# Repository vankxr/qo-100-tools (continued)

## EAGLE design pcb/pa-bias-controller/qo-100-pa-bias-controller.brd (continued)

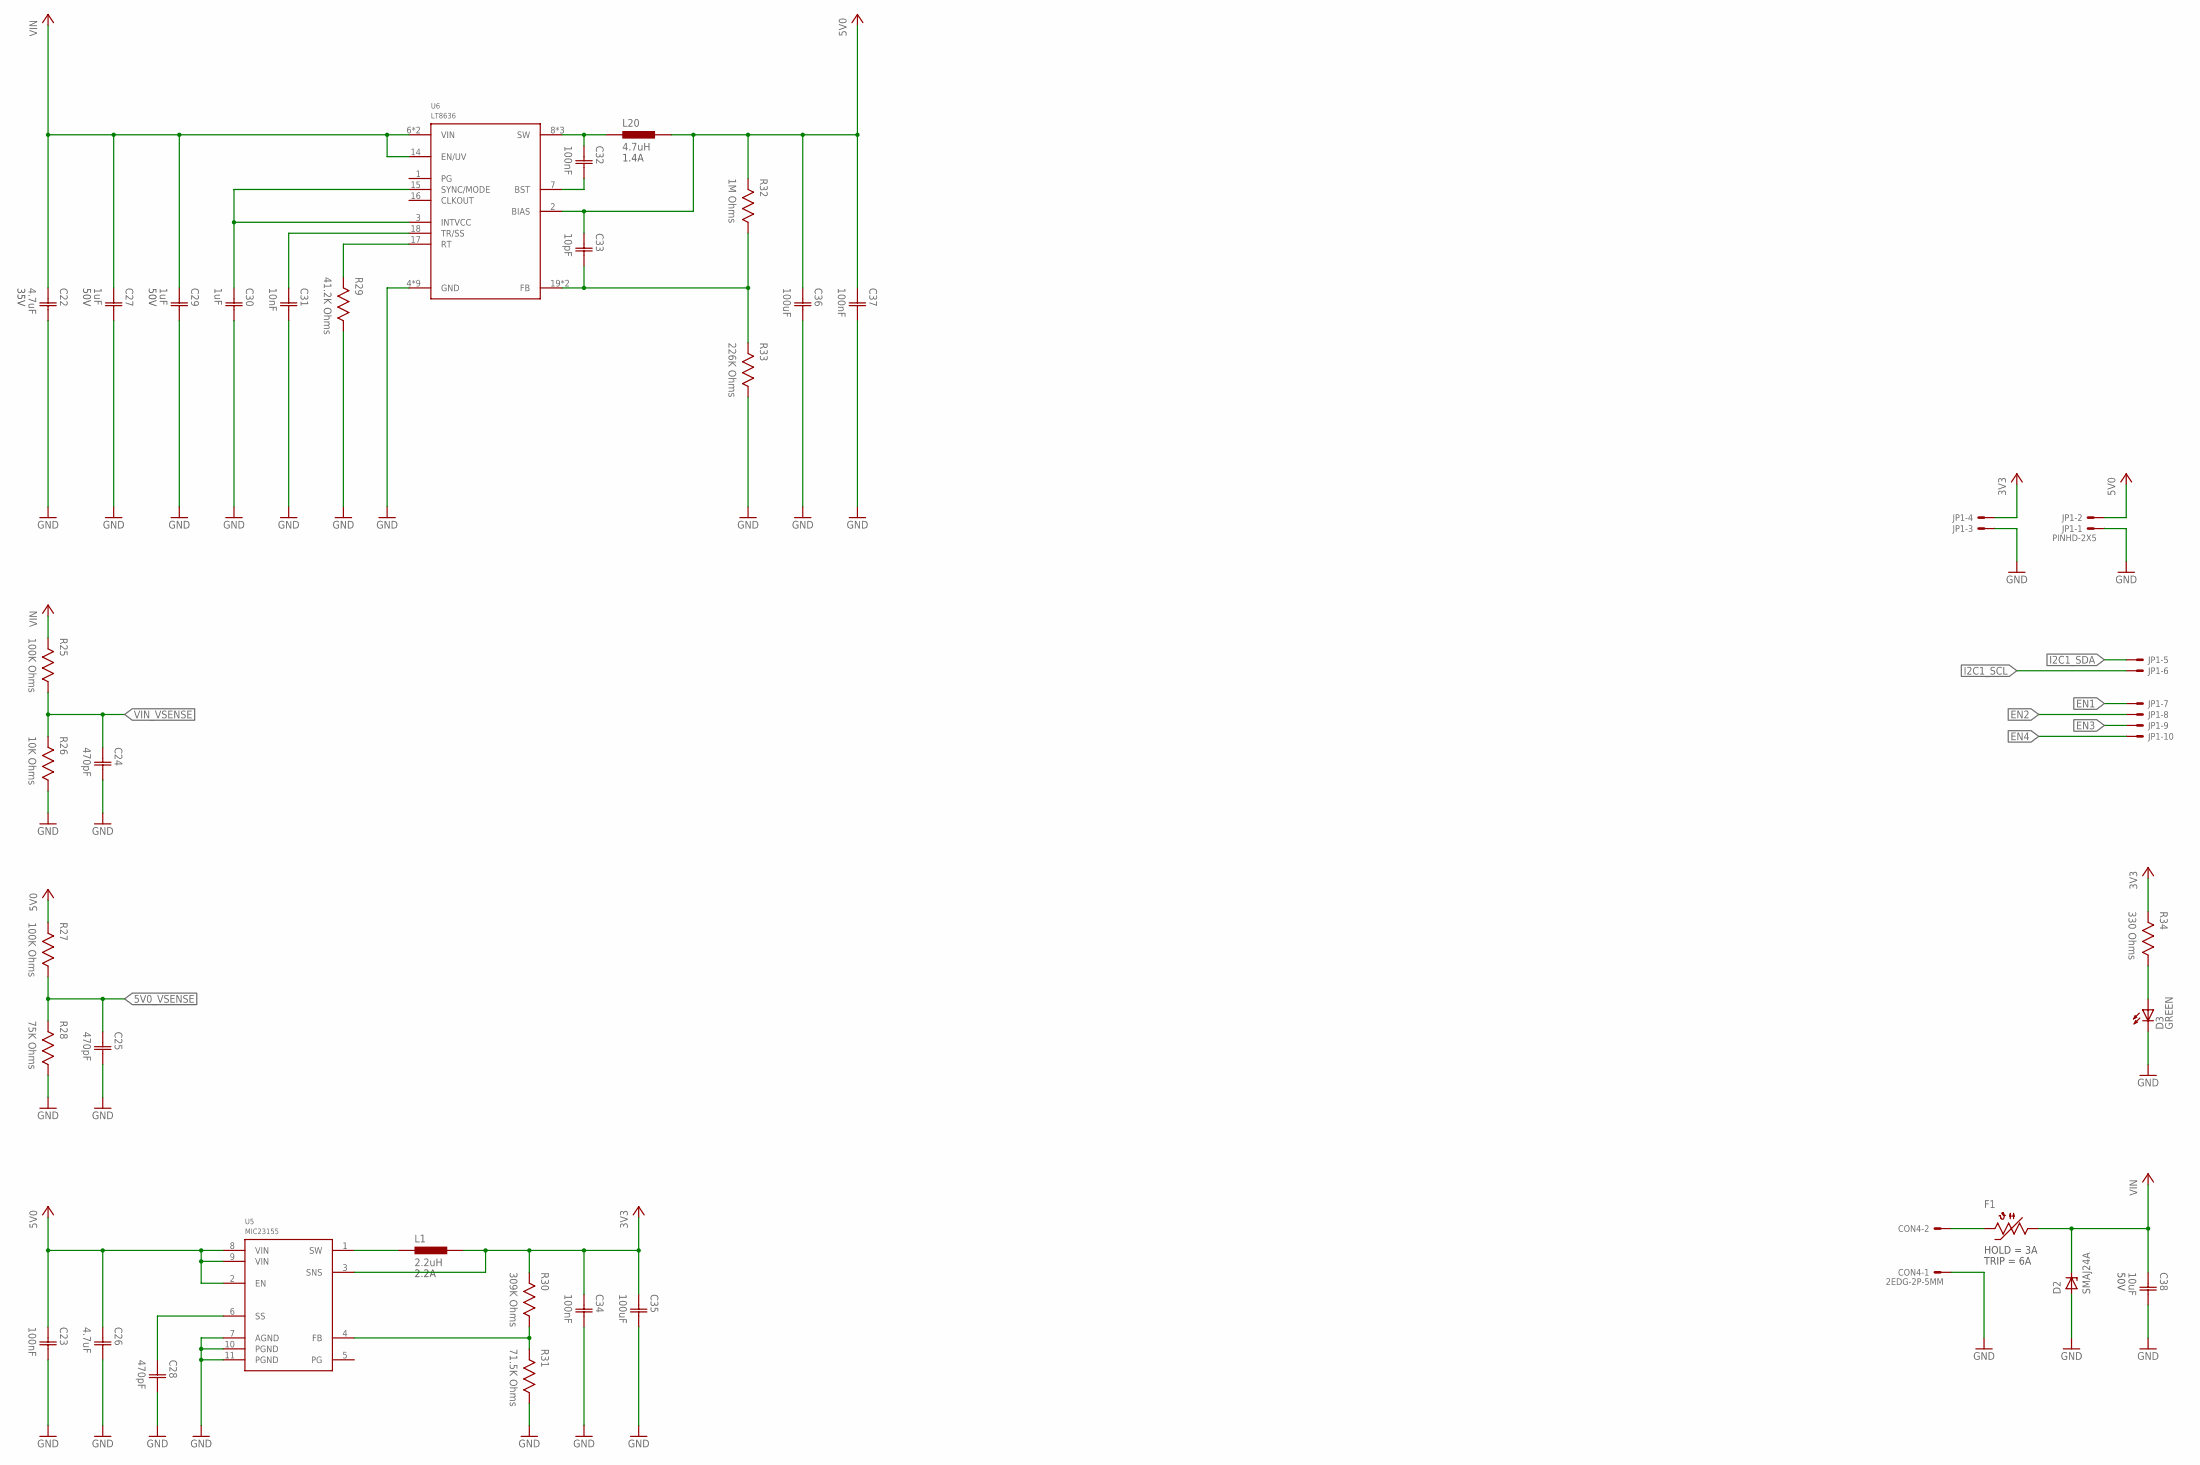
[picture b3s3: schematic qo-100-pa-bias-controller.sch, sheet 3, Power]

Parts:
C22: 4.7uF; CAP0603; VOLTAGE 35V
C23, C32, C34, C37: 100nF; CAP0603
C24, C25, C28: 470pF; CAP0603
C26: 4.7uF; CAP0603
C27, C29: 1uF; CAP0603; VOLTAGE 50V
C30: 1uF; CAP0603
C31: 10nF; CAP0603
C33: 10pF; CAP0603
C35, C36: 100uF; CAP1206
C38: 10uF; CAP1206; VOLTAGE 50V
CON4: 2EDG-2P-5MM
D2: SMAJ24A; DO214AC
D3: LED0603; 0603
F1: 2.6A Hold; 1206
JP1: PINHD-2X5; 2X05
L1: 2.2uH; IND2520
L20: 4.7uH; IND2520
R25, R27: 100K Ohms; RES0603
R26: 10K Ohms; RES0603
R28: 75K Ohms; RES0603
R29: 41.2K Ohms; RES0603
R30: 309K Ohms; RES0603
R31: 71.5K Ohms; RES0603
R32: 1M Ohms; RES0603
R33: 226K Ohms; RES0603
R34: 330 Ohms; RES0603
U5: MIC23155; DFN10
U6: LT8636; QFN20_ASYM_CORNER

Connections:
3V3: C34.1 (C1), C35.1 (C1), JP1.4, L1.2, R30.2, R34.2, U5.3 (SNS); also elsewhere on the board
3V3_FB: R30.1, R31.2, U5.4 (FB)
3V3_SOFTSTART: C28.1 (C1), U5.6 (SS)
3V3_SW: L1.1, U5.1 (SW)
5V0: C23.1 (C1), C26.1 (C1), C33.1 (C1), C36.1 (C1), C37.1 (C1), JP1.2, L20.2, R27.2, R32.2, U5.2 (EN), U5.8 (VIN), U5.9 (VIN), U6.2 (BIAS); also elsewhere on the board
5V0_BST: C32.2 (C2), U6.7 (BST)
5V0_FB: C33.2 (C2), R32.1, R33.2, U6.19 (FB), U6.20 (FB)
5V0_INTVCC: C30.1 (C1), U6.3 (INTVCC), U6.15 (SYNC/MODE)
5V0_RT: R29.2, U6.17 (RT)
5V0_SS: C31.1 (C1), U6.18 (TR/SS)
5V0_SW: C32.1 (C1), L20.1, U6.8 (SW), U6.9 (SW), U6.10 (SW)
5V0_VSENSE: C25.1 (C1), R27.1, R28.2; also elsewhere on the board
EN1: JP1.7; also elsewhere on the board
EN2: JP1.8; also elsewhere on the board
EN3: JP1.9; also elsewhere on the board
EN4: JP1.10; also elsewhere on the board
GND: C22.2 (C2), C23.2 (C2), C24.2 (C2), C25.2 (C2), C26.2 (C2), C27.2 (C2), C28.2 (C2), C29.2 (C2), C30.2 (C2), C31.2 (C2), C34.2 (C2), C35.2 (C2), C36.2 (C2), C37.2 (C2), C38.2 (C2), CON4.P$1, D2.A, D3.C, JP1.1, JP1.3, R26.1, R28.1, R29.1, R31.1, R33.1, U5.7 (AGND), U5.10 (PGND), U5.11 (PGND), U6.4 (GND), U6.5 (GND), U6.12 (GND), U6.13 (GND), U6.21 (GND), U6.M1 (GND), U6.M2 (GND), U6.M3 (GND), U6.M4 (GND); also elsewhere on the board
I2C1_SCL: JP1.6; also elsewhere on the board
I2C1_SDA: JP1.5; also elsewhere on the board
unnamed: CON4.P$2, F1.2
unnamed: D3.A, R34.1
VIN: C22.1 (C1), C27.1 (C1), C29.1 (C1), C38.1 (C1), D2.C, F1.1, R25.2, U6.6 (VIN), U6.11 (VIN), U6.14 (EN/UV)
VIN_VSENSE: C24.1 (C1), R25.1, R26.2; also elsewhere on the board

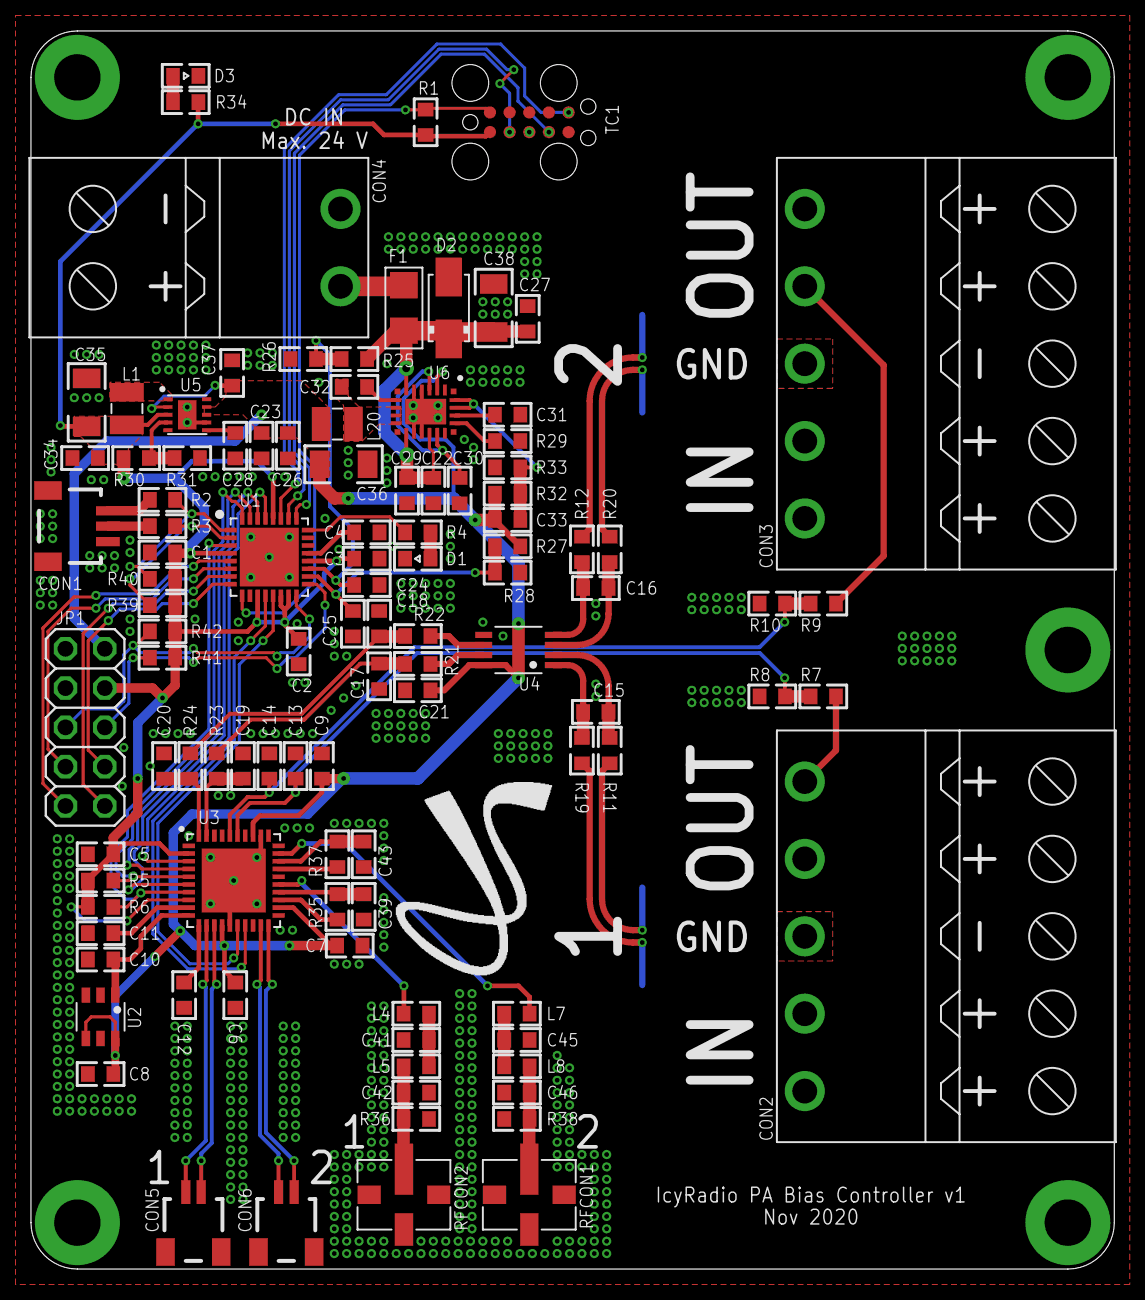
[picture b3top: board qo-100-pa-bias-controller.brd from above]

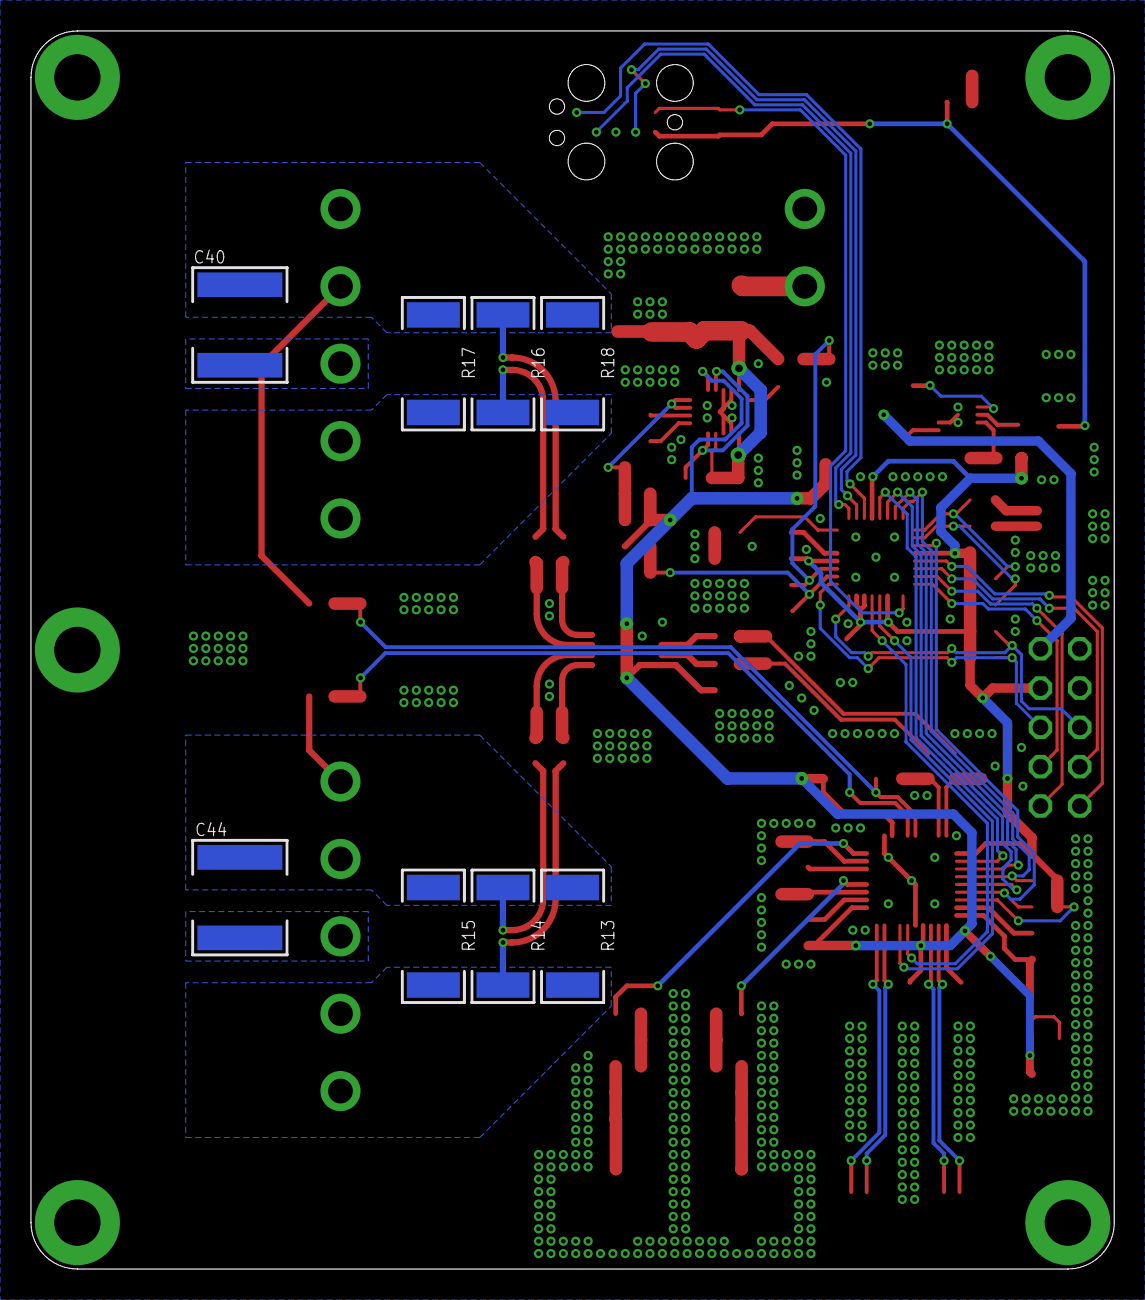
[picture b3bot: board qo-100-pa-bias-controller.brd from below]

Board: 2 copper layers, 70.0 x 80.0 mm, 115 parts (8 on the bottom side), 74 nets.

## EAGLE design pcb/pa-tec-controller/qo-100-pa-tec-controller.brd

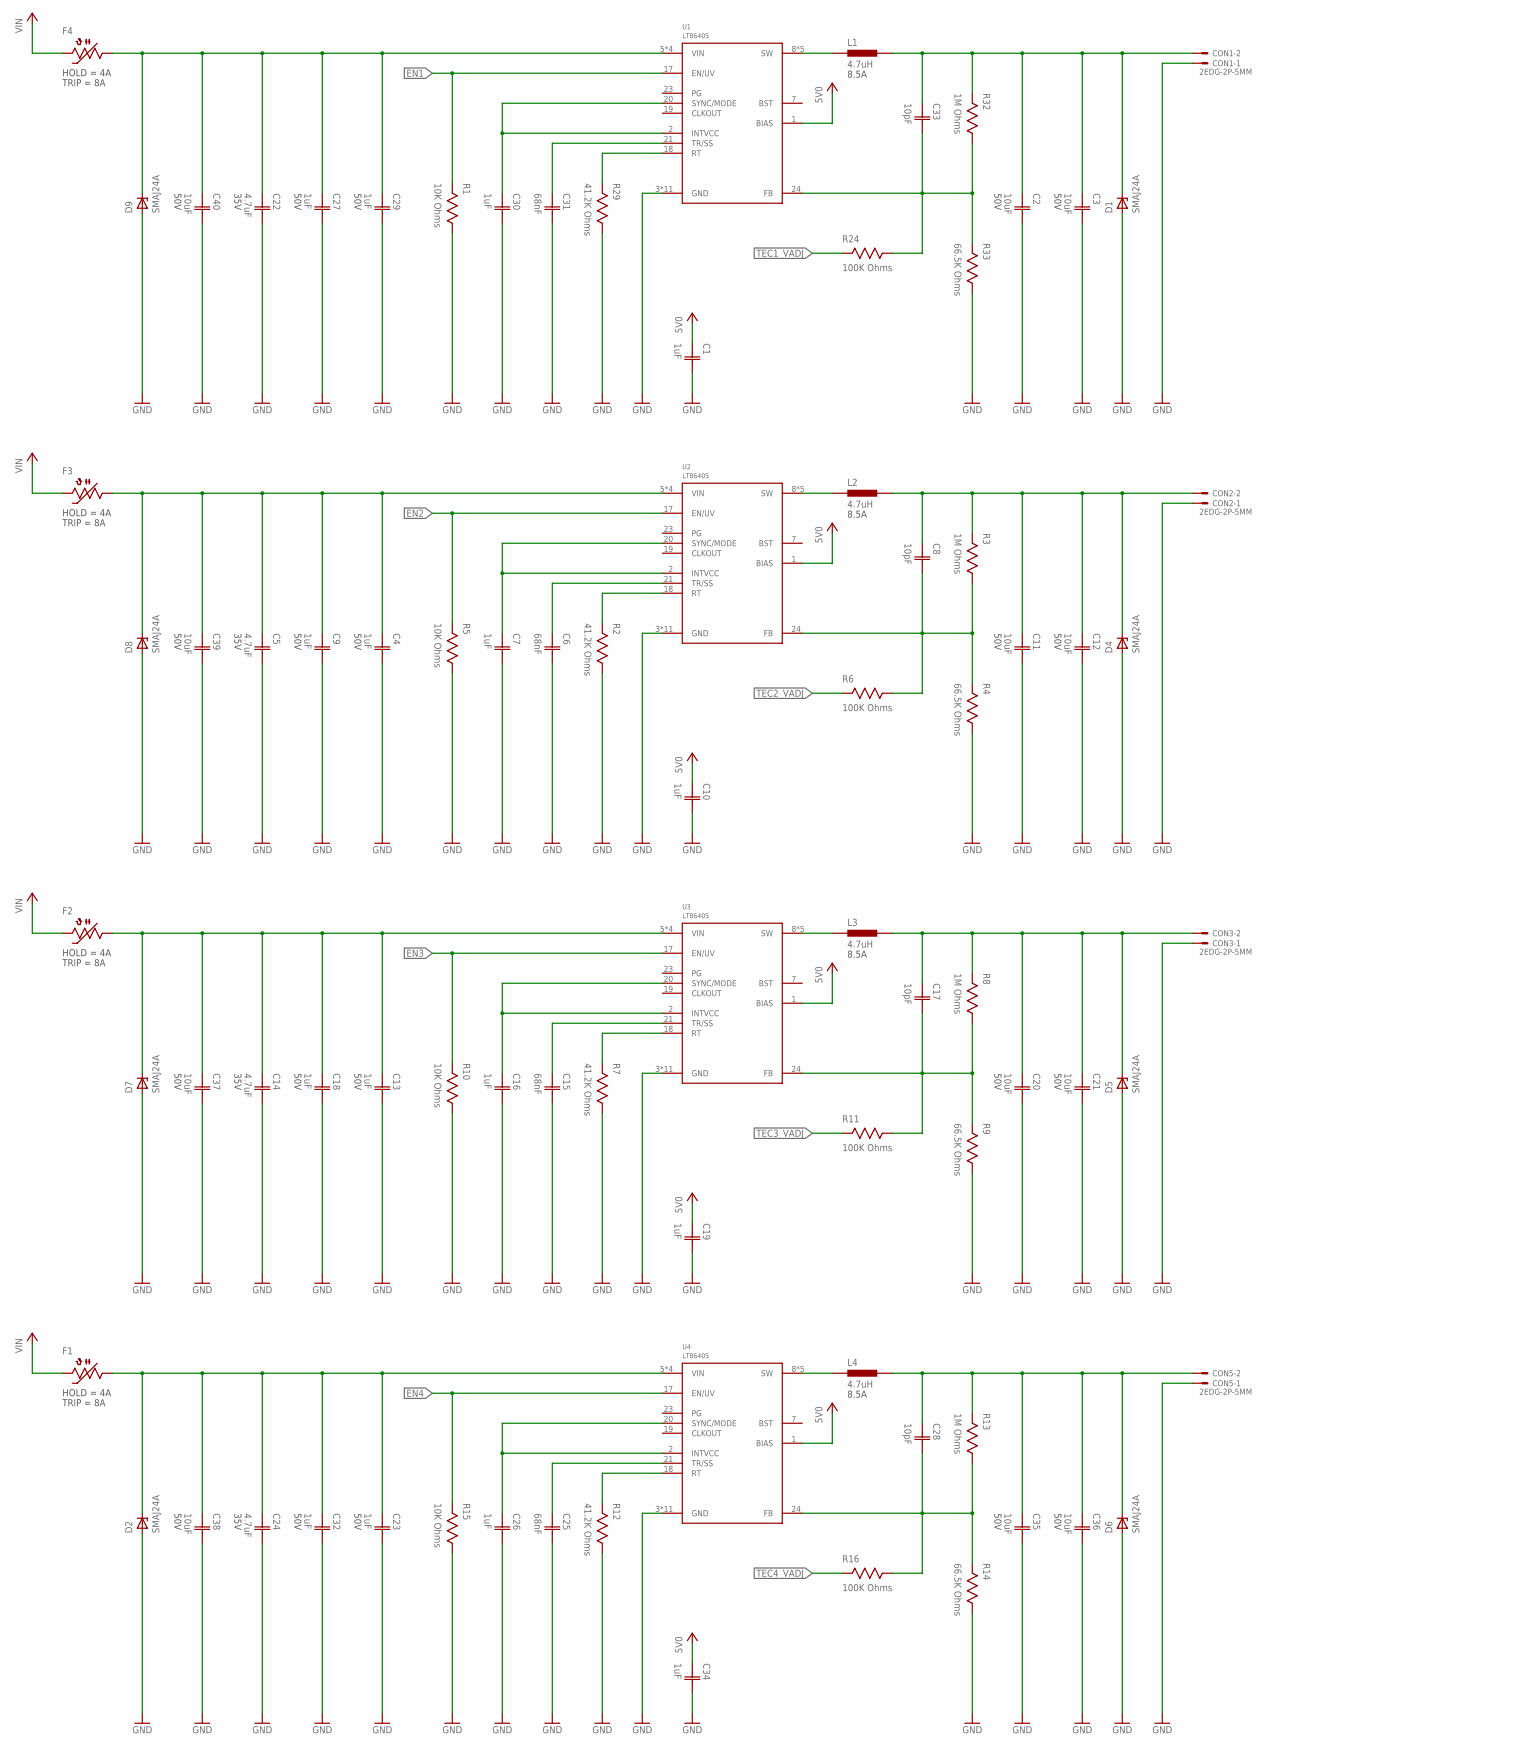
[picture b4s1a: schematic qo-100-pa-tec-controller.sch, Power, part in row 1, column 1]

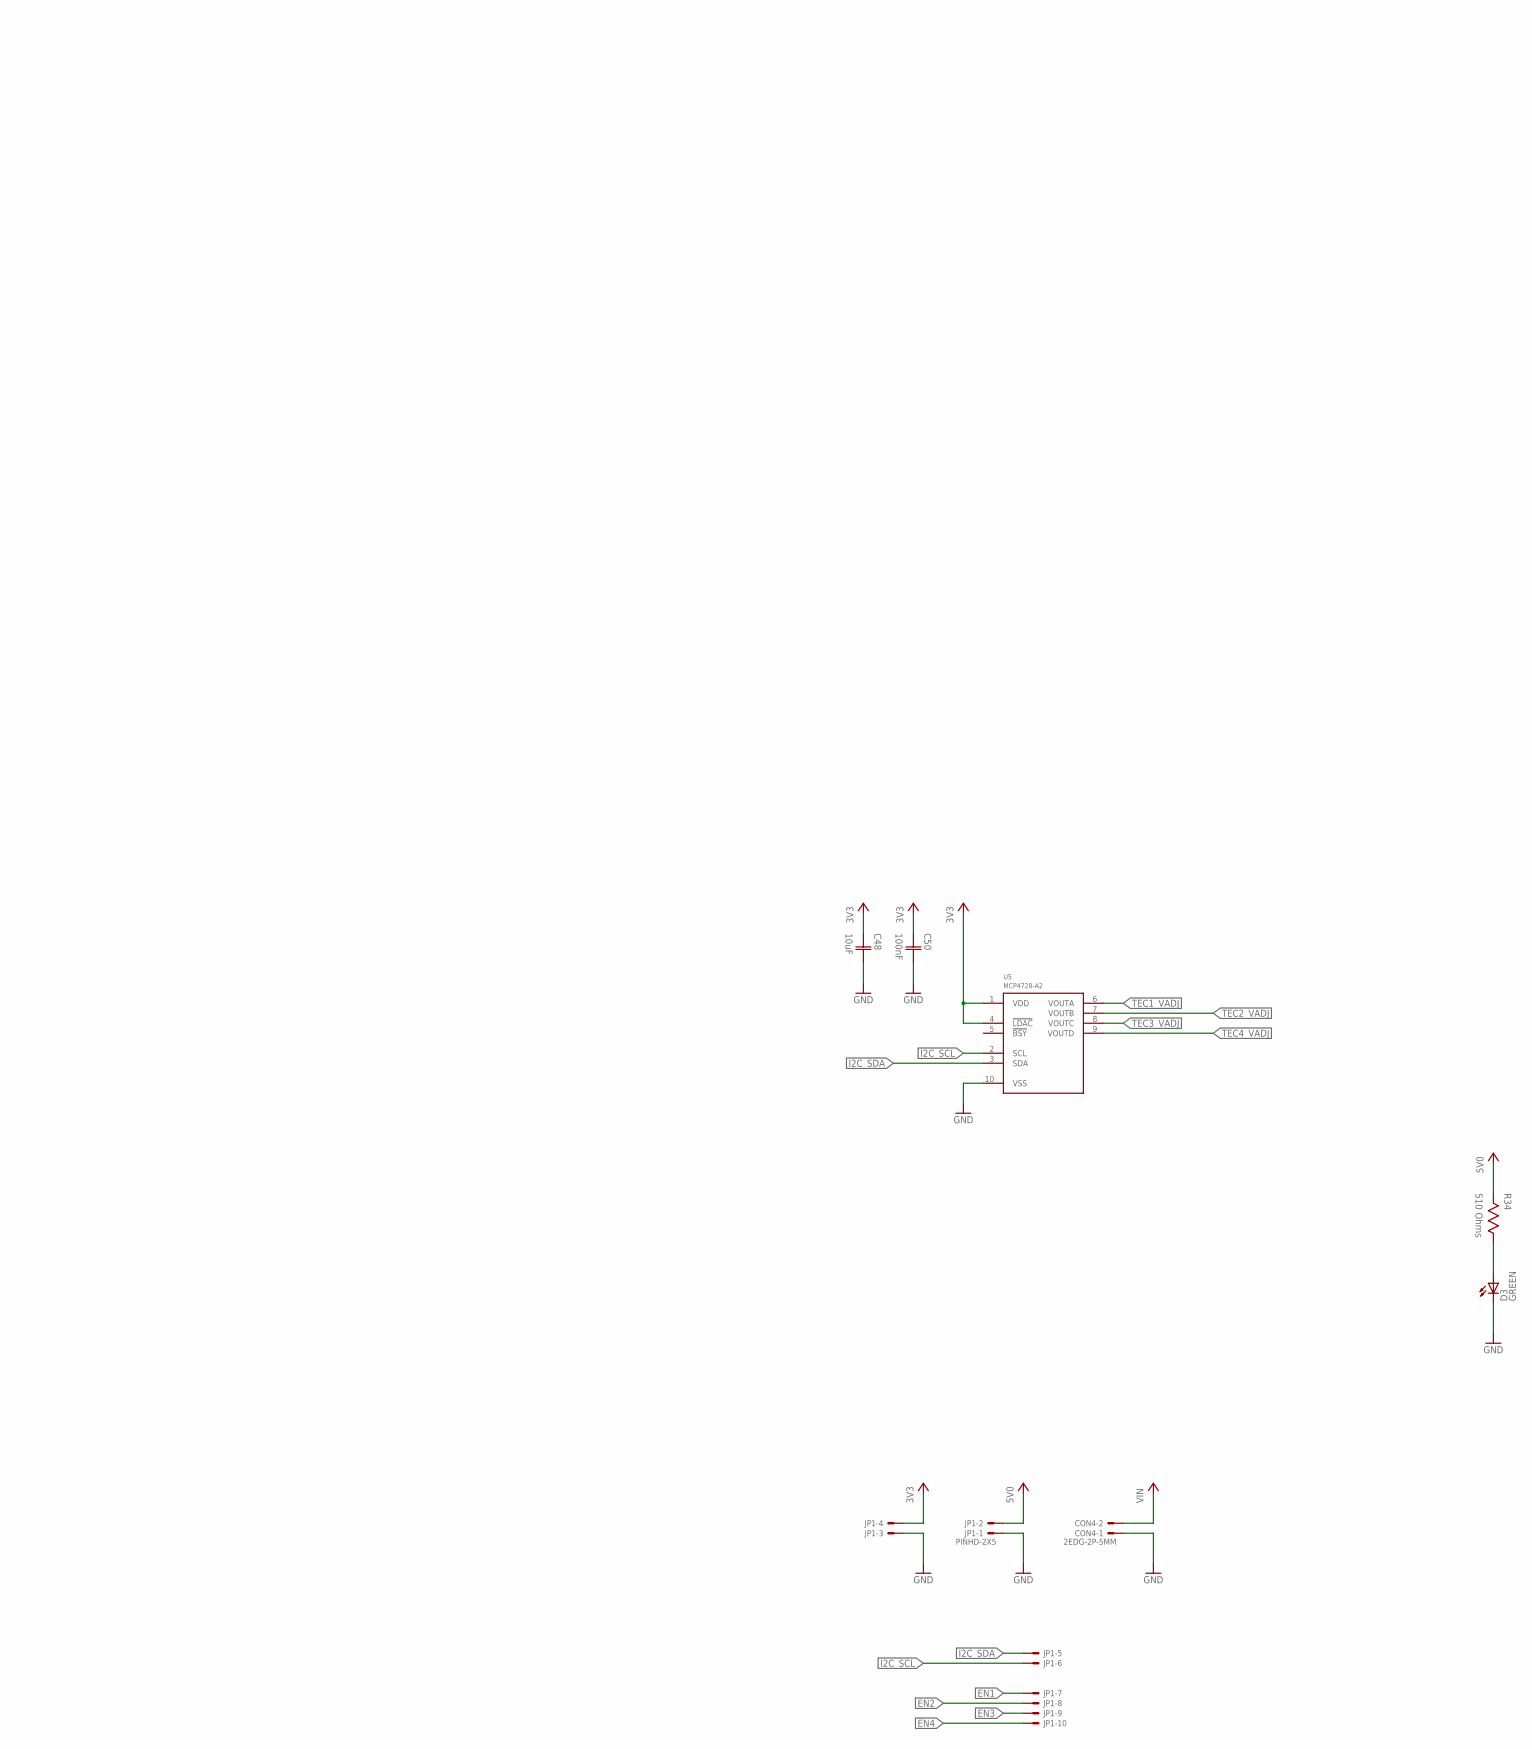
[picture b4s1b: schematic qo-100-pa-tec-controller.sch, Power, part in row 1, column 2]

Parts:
C1, C7, C10, C16, C19, C26, C30, C34: 1uF; CAP0603
C2, C3, C11, C12, C20, C21, C35, C36, C37, C38, C39, C40: 10uF; CAP1206; VOLTAGE 50V
C4, C9, C13, C18, C23, C27, C29, C32: 1uF; CAP0603; VOLTAGE 50V
C5, C14, C22, C24: 4.7uF; CAP0603; VOLTAGE 35V
C6, C15, C25, C31: 68nF; CAP0603
C8, C17, C28, C33: 10pF; CAP0603
C48: 10uF; CAP0603
C50: 100nF; CAP0603
CON1, CON2, CON3, CON4, CON5: 2EDG-2P-5MM
D1, D2, D4, D5, D6, D7, D8, D9: SMAJ24A; DO214AC
D3: LED0603; 0603
F1, F2, F3, F4: 2.6A Hold; 1206
JP1: PINHD-2X5; 2X05
L1, L2, L3, L4: 4.7uH; IND1040
R1, R5, R10, R15: 10K Ohms; RES0603
R2, R7, R12, R29: 41.2K Ohms; RES0603
R3, R8, R13, R32: 1M Ohms; RES0603
R4, R9, R14, R33: 66.5K Ohms; RES0603
R6, R11, R16, R24: 100K Ohms; RES0603
R34: 510 Ohms; RES0603
U1, U2, U3, U4: LT8640S; QFN24_CORNER
U5: MCP4728-A2; MSOP10

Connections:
3V3: C48.1 (C1), C50.1 (C1), JP1.4, U5.1 (VDD), U5.4 (!LDAC)
5V0: C1.1 (C1), C10.1 (C1), C19.1 (C1), C34.1 (C1), JP1.2, R34.2, U1.1 (BIAS), U2.1 (BIAS), U3.1 (BIAS), U4.1 (BIAS)
EN1: JP1.7, R1.2, U1.17 (EN/UV)
EN2: JP1.8, R5.2, U2.17 (EN/UV)
EN3: JP1.9, R10.2, U3.17 (EN/UV)
EN4: JP1.10, R15.2, U4.17 (EN/UV)
GND: C1.2 (C2), C2.2 (C2), C3.2 (C2), C4.2 (C2), C5.2 (C2), C6.2 (C2), C7.2 (C2), C9.2 (C2), C10.2 (C2), C11.2 (C2), C12.2 (C2), C13.2 (C2), C14.2 (C2), C15.2 (C2), C16.2 (C2), C18.2 (C2), C19.2 (C2), C20.2 (C2), C21.2 (C2), C22.2 (C2), C23.2 (C2), C24.2 (C2), C25.2 (C2), C26.2 (C2), C27.2 (C2), C29.2 (C2), C30.2 (C2), C31.2 (C2), C32.2 (C2), C34.2 (C2), C35.2 (C2), C36.2 (C2), C37.2 (C2), C38.2 (C2), C39.2 (C2), C40.2 (C2), C48.2 (C2), C50.2 (C2), CON1.P$1, CON2.P$1, CON3.P$1, CON4.P$1, CON5.P$1, D1.A, D2.A, D3.C, D4.A, D5.A, D6.A, D7.A, D8.A, D9.A, JP1.1, JP1.3, R1.1, R2.1, R4.1, R5.1, R7.1, R9.1, R10.1, R12.1, R14.1, R15.1, R29.1, R33.1, U1.3 (GND), U1.16 (GND), U1.22 (GND), U1.25 (GND), U1.26 (GND), U1.27 (GND), U1.28 (GND), U1.29 (GND), U1.30 (GND), U1.31 (GND), U1.32 (GND), U2.3 (GND), U2.16 (GND), U2.22 (GND), U2.25 (GND), U2.26 (GND), U2.27 (GND), U2.28 (GND), U2.29 (GND), U2.30 (GND), U2.31 (GND), U2.32 (GND), U3.3 (GND), U3.16 (GND), U3.22 (GND), U3.25 (GND), U3.26 (GND), U3.27 (GND), U3.28 (GND), U3.29 (GND), U3.30 (GND), U3.31 (GND), U3.32 (GND), U4.3 (GND), U4.16 (GND), U4.22 (GND), U4.25 (GND), U4.26 (GND), U4.27 (GND), U4.28 (GND), U4.29 (GND), U4.30 (GND), U4.31 (GND), U4.32 (GND), U5.10 (VSS)
I2C_SCL: JP1.6, U5.2 (SCL)
I2C_SDA: JP1.5, U5.3 (SDA)
unnamed: D3.A, R34.1
TEC1_VADJ: R24.2, U5.6 (VOUTA)
TEC1_VIN: C22.1 (C1), C27.1 (C1), C29.1 (C1), C40.1 (C1), D9.C, F4.1, U1.5 (VIN), U1.6 (VIN), U1.13 (VIN), U1.14 (VIN)
TEC2_VADJ: R6.2, U5.7 (VOUTB)
TEC2_VIN: C4.1 (C1), C5.1 (C1), C9.1 (C1), C39.1 (C1), D8.C, F3.1, U2.5 (VIN), U2.6 (VIN), U2.13 (VIN), U2.14 (VIN)
TEC3_VADJ: R11.2, U5.8 (VOUTC)
TEC3_VIN: C13.1 (C1), C14.1 (C1), C18.1 (C1), C37.1 (C1), D7.C, F2.1, U3.5 (VIN), U3.6 (VIN), U3.13 (VIN), U3.14 (VIN)
TEC4_VADJ: R16.2, U5.9 (VOUTD)
TEC4_VIN: C23.1 (C1), C24.1 (C1), C32.1 (C1), C38.1 (C1), D2.C, F1.1, U4.5 (VIN), U4.6 (VIN), U4.13 (VIN), U4.14 (VIN)
VIN: CON4.P$2, F1.2, F2.2, F3.2, F4.2
VTEC1: C2.1 (C1), C3.1 (C1), C33.1 (C1), CON1.P$2, D1.C, L1.2, R32.2
VTEC1_FB: C33.2 (C2), R24.1, R32.1, R33.2, U1.24 (FB)
VTEC1_INTVCC: C30.1 (C1), U1.2 (INTVCC), U1.20 (SYNC/MODE)
VTEC1_RT: R29.2, U1.18 (RT)
VTEC1_SS: C31.1 (C1), U1.21 (TR/SS)
VTEC1_SW: L1.1, U1.8 (SW), U1.9 (SW), U1.10 (SW), U1.11 (SW), U1.12 (SW)
VTEC2: C8.1 (C1), C11.1 (C1), C12.1 (C1), CON2.P$2, D4.C, L2.2, R3.2
VTEC2_FB: C8.2 (C2), R3.1, R4.2, R6.1, U2.24 (FB)
VTEC2_INTVCC: C7.1 (C1), U2.2 (INTVCC), U2.20 (SYNC/MODE)
VTEC2_RT: R2.2, U2.18 (RT)
VTEC2_SS: C6.1 (C1), U2.21 (TR/SS)
VTEC2_SW: L2.1, U2.8 (SW), U2.9 (SW), U2.10 (SW), U2.11 (SW), U2.12 (SW)
VTEC3: C17.1 (C1), C20.1 (C1), C21.1 (C1), CON3.P$2, D5.C, L3.2, R8.2
VTEC3_FB: C17.2 (C2), R8.1, R9.2, R11.1, U3.24 (FB)
VTEC3_INTVCC: C16.1 (C1), U3.2 (INTVCC), U3.20 (SYNC/MODE)
VTEC3_RT: R7.2, U3.18 (RT)
VTEC3_SS: C15.1 (C1), U3.21 (TR/SS)
VTEC3_SW: L3.1, U3.8 (SW), U3.9 (SW), U3.10 (SW), U3.11 (SW), U3.12 (SW)
VTEC4: C28.1 (C1), C35.1 (C1), C36.1 (C1), CON5.P$2, D6.C, L4.2, R13.2
VTEC4_FB: C28.2 (C2), R13.1, R14.2, R16.1, U4.24 (FB)
VTEC4_INTVCC: C26.1 (C1), U4.2 (INTVCC), U4.20 (SYNC/MODE)
VTEC4_RT: R12.2, U4.18 (RT)
VTEC4_SS: C25.1 (C1), U4.21 (TR/SS)
VTEC4_SW: L4.1, U4.8 (SW), U4.9 (SW), U4.10 (SW), U4.11 (SW), U4.12 (SW)

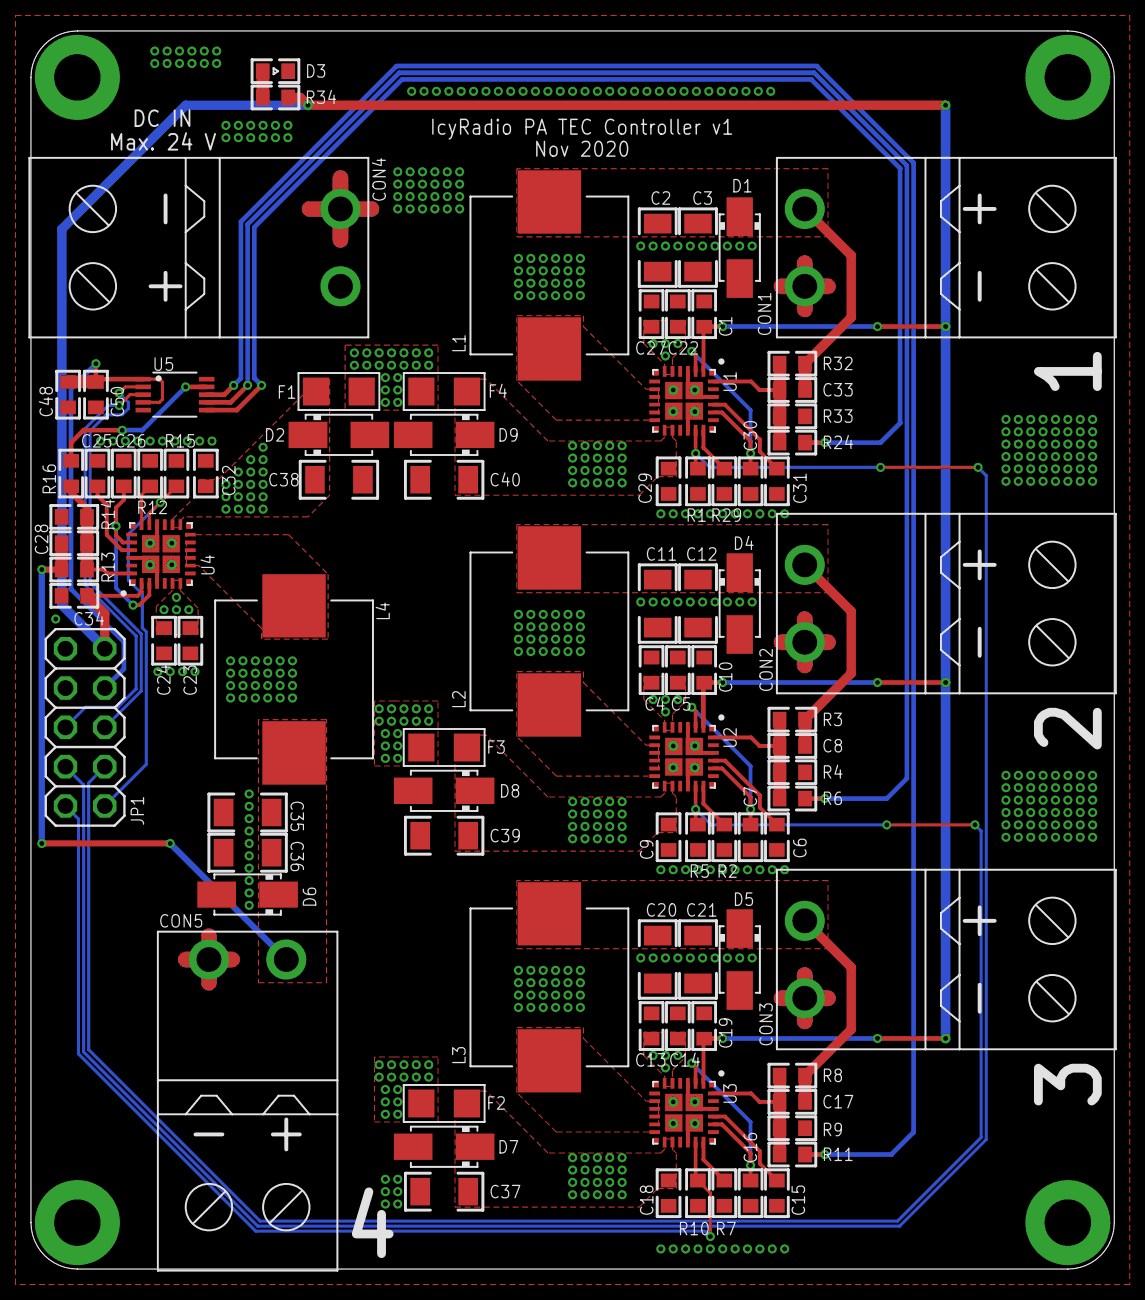
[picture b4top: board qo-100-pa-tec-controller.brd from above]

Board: 2 copper layers, 70.0 x 80.0 mm, 91 parts (0 on the bottom side), 43 nets.
